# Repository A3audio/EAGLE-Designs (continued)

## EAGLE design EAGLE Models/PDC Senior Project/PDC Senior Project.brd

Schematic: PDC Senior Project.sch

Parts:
C1, C2: 18pF; C0805
C3, C4: 2.2uF; C0603
C5, C6, C7, C8, C9, C10, C11, C13, C14, C17, C21, C22: 220p; C0603
C12, C18, C19, C20: 100n; C0805
C16: 4.7nF; 0805
C23, C24: 10uF; C0603
D1: 1N4148; SOD-123
D2: 1N5819; SOD123
F1: 16V,0.25A; PTC-1206
F2, F3, F4, F5, F6, F7, F8, F9: PTC_FUSE2002920L; 2920L
H1, H2, H3, H4: MOUNT-PAD-ROUND#4-40-PAD; #4-40-PAD-ROUND
H7: ICSP; 2X3_SMD_FCI_54202-G30
IC1: AT90CAN128; TQFP64
IC2: MCP2551SO8; SO08
IC3: NUP2105L; SOT-23
IC5: FT232RL; SSOP28
L1: CS321613-100K; L3216C
LED2: RX; CHIPLED_0805
LED3: TX; CHIPLED_0805
M1, M2, M3, M4, M5, M6, M7, M8, M9, M11, M12: PSMN2R2-25YLC; SOT669(LFPAK_POWER-SO8)
Q1: 56P2859; HC49UP
R1, R3: 100K; R0805
R2, R7, R8, R9: 1k; R0805
R4, R11, R13, R15: 3k; R0603
R5, R10, R12, R14, R16, R18, R20, R22, R24, R26, R28, R30, R32, R34, R36, R38, R40, R49: 10k; R0603
R6: 1K; R0805
R17, R19, R21, R23, R25, R27, R29, R31, R33, R35, R37, R39, R48: 26k; R0603
R41, R42, R43, R44, R45, R46: 2k1; R0603
R47: 14k7; R0603
RS1, RS2, RS3, RS4: 0.002; WSL2726_RES
SJ1: SOLDERJUMPERNO; SJ_2S-NO
U1, U7, U8, U9, U10, U13, U14, U15, U16, U17, U18, U19: LT6100HMS8PBF; SOP65P490X110-8N
U2, U4, U5, U6: LT1716IS5PBF; SOT95P280X100-5N
U3, U11, U12: LT1161ISWPBF; SOIC127P1032X264-20N
U20: DG409DY-E3; SOIC127P600X175-16N
U21: AD5314WARMZ-REEL7; SOP50P490X110-10N
U22: LT1910IS8TRPBF; SOIC127P600X175-8N
U$2: MMPQ3904; SOIC16NB
U$3: MMPQ3906; SOIC16NB
U$4, U$6, U$8, U$10, U$12, U$14, U$16, U$18: 0.02; LVK2010
U$4V5V: MAX6350CSA; 8-SOIC
U$5, U$7, U$9, U$11, U$13, U$15, U$17, U$19: PSMN2R2-25YLC; SOT669(LFPAK_POWER-SO8)
U$20: DG407; PLCC28S
U$21: MCP970X; SOT23
U$22, U$23, U$24: AZ23C4V7-7-F; SOT23-3
U$25: SUPERSEAL1.0_60POS
U$26: NCP1117; SOT-223-4
VCC!: PWR; CHIPLED_0805

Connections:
5VREF: C4.1, IC1.62 (AREF), U$4V5V.P6
5V_REG_IN: C23.1, D2.C, U$26.3 (INPUT)
12V: C3.1, D2.A, F2.1, F3.1, F4.1, F5.1, F6.1, F7.1, F8.1, F9.1, R47.2, R48.1, RS1.PAS1 (1), RS2.PAS2 (2), RS3.PAS2 (2), RS4.PAS1 (1), U3.11 (V+_2), U3.13 (SEN_4), U3.15 (SEN_3), U3.17 (SEN_2), U3.19 (SEN_1), U3.20 (V+), U11.11 (V+_2), U11.13 (SEN_4), U11.15 (SEN_3), U11.17 (SEN_2), U11.19 (SEN_1), U11.20 (V+), U12.11 (V+_2), U12.13 (SEN_4), U12.15 (SEN_3), U12.17 (SEN_2), U12.19 (SEN_1), U12.20 (V+), U22.4 (IN), U22.6 (SENSE), U22.8 (V+), U$4V5V.P2, U$25.B1, U$25.B2, U$25.B8
ADC0: IC1.61 (PF0(ADC0)), U$20.28 (DA)
ADC1: IC1.60 (PF1(ADC1)), U$20.2 (DB)
ADC2: IC1.59 (PF2(ADC2)), U20.8 (DA)
ADC3: IC1.58 (PF3(ADC3)), U20.9 (DB)
ANALOG_EMERGENCY_SHUTDOWN: R10.2, U$3.9 (B4), U$3.11 (B3), U$3.13 (B2), U$3.15 (B1), U$25.A4
AVR_CS: IC1.10 ((SS)PB0), U21.10 (~SYNC)
AVR_MISO: IC1.13 ((MISO)PB3)
AVR_MOSI: IC1.12 ((MOSI)PB2), U21.8 (DIN)
AVR_SCK: H7.3, IC1.11 ((SCK)PB1), U21.9 (SCLK)
BAT_SENSE: IC1.54 (PF7(ADC7/TDI)), R48.2, R49.1
CAN_H: IC2.7 (CANH), IC3.2, U$25.A29
CAN_L: IC2.6 (CANL), IC3.1, U$25.A30
D+: IC5.15 (USBDP), U$25.A27
D-: IC5.16 (USBDM), U$25.A28
DTR: C20.1, IC5.2 (DTR#)
GND: C1.1, C2.1, C3.2, C4.2, C5.2, C6.2, C7.2, C8.2, C9.2, C10.2, C11.2, C12.2, C13.2, C14.2, C16.2, C17.2, C18.2, C19.2, C21.2, C22.2, C23.2, C24.2, H1.P$1, H2.P$1, H3.P$1, H4.P$1, H7.6, IC1.22 (GND), IC1.53 (GND_53), IC1.63 (GND(A)), IC2.2 (GND), IC3.3, IC5.7 (GND1), IC5.18 (GND2), IC5.21 (GND3), IC5.25 (AGND), IC5.26 (TEST), R3.2, R18.2, R20.2, R22.2, R24.2, R26.2, R28.2, R30.2, R32.2, R34.2, R36.2, R38.2, R40.2, R49.2, SJ1.1, U1.4 (VEE), U1.6 (A2), U1.7 (A4), U2.2 (V-), U3.1 (GND_2), U3.10 (GND), U4.2 (V-), U5.2 (V-), U6.2 (V-), U7.4 (VEE), U7.6 (A2), U7.7 (A4), U8.4 (VEE), U8.6 (A2), U8.7 (A4), U9.4 (VEE), U9.6 (A2), U9.7 (A4), U10.4 (VEE), U10.7 (A4), U11.1 (GND_2), U11.10 (GND), U12.1 (GND_2), U12.10 (GND), U13.4 (VEE), U13.7 (A4), U14.4 (VEE), U14.7 (A4), U15.4 (VEE), U15.7 (A4), U16.4 (VEE), U16.7 (A4), U17.4 (VEE), U17.7 (A4), U18.4 (VEE), U18.7 (A4), U19.4 (VEE), U19.7 (A4), U20.3 (V-), U20.15 (GND), U21.7 (GND), U22.1 (GND), U$2.10 (E4), U$2.12 (E3), U$2.14 (E2), U$2.16 (E1), U$4V5V.P4, U$20.12 (GND), U$20.27 (V-), U$21.3 (GND), U$22.3, U$23.3, U$24.3, U$25.A7, U$25.A8, U$25.A9, U$25.A15, U$25.A16, U$25.A17, U$25.A19, U$25.A24, U$25.A25, U$25.A32, U$25.A33, U$25.A34, U$25.B3, U$25.B9, U$25.B10, U$25.B14, U$25.B15, U$25.B16, U$25.B20, U$25.B21, U$25.B22, U$25.B23, U$26.1 (ADJUST), VCC!.C
HC1_ANALOG_BACKUP_REF: U2.4 (-IN), U21.2 (VOUTA)
HC1_DISCH_TRIGGER: R5.2, U2.1 (OUT), U$2.15 (B1)
HC1_GATE: M2.4 (G), M3.4 (G), U3.18 (GATE_1), U$2.1 (C1_A), U$2.2 (C1_B)
HC1_GATE_IN: U3.3 (INPUT_1), U$3.1 (C1_A), U$3.2 (C1_B)
HC1_ISENSE: R4.1, U1.5 (VOUT), U20.5 (S2A)
HC1_OUTPUT: M2.1 (S1), M2.2 (S2), M2.3 (S3), M3.1 (S1), M3.2 (S2), M3.3 (S3), R39.1, U$25.B5, U$25.B11
HC1_VSENSE: R39.2, R40.1, U20.12 (S2B)
HC2_ANALOG_BACKUP_REF: U4.4 (-IN), U21.3 (VOUTB)
HC2_DISCH_TRIGGER: R12.2, U4.1 (OUT), U$2.13 (B2)
HC2_GATE: M5.4 (G), M6.4 (G), U3.16 (GATE_2), U$2.3 (C2_A), U$2.4 (C2_B)
HC2_GATE_IN: U3.5 (INPUT_2), U$3.3 (C2_A), U$3.4 (C2_B)
HC2_ISENSE: R11.1, U7.5 (VOUT), U20.7 (S4A)
HC2_OUTPUT: M5.1 (S1), M5.2 (S2), M5.3 (S3), M6.1 (S1), M6.2 (S2), M6.3 (S3), R37.1, U$25.A2, U$25.A11
HC2_VSENSE: R37.2, R38.1, U20.10 (S4B)
HC3_ANALOG_BACKUP_REF: U5.4 (-IN), U21.4 (VOUTC)
HC3_DISCH_TRIGGER: R14.2, U5.1 (OUT), U$2.11 (B3)
HC3_GATE: M8.4 (G), M9.4 (G), U3.14 (GATE_3), U$2.5 (C3_A), U$2.6 (C3_B)
HC3_GATE_IN: U3.7 (INPUT_3), U$3.5 (C3_A), U$3.6 (C3_B)
HC3_ISENSE: R13.1, U8.5 (VOUT), U20.6 (S3A)
HC3_OUTPUT: M8.1 (S1), M8.2 (S2), M8.3 (S3), M9.1 (S1), M9.2 (S2), M9.3 (S3), R35.1, U$25.A3, U$25.A12
HC3_VSENSE: R35.2, R36.1, U20.11 (S3B)
HC4_ANALOG_BACKUP_REF: U6.4 (-IN), U21.6 (VOUTD)
HC4_DISCH_TRIGGER: R16.2, U6.1 (OUT), U$2.9 (B4)
HC4_GATE: M11.4 (G), M12.4 (G), U3.12 (GATE_4), U$2.7 (C4_A), U$2.8 (C4_B)
HC4_GATE_IN: U3.9 (INPUT_4), U$3.7 (C4_A), U$3.8 (C4_B)
HC4_ISENSE: R15.1, U9.5 (VOUT), U20.4 (S1A)
HC4_OUTPUT: M11.1 (S1), M11.2 (S2), M11.3 (S3), M12.1 (S1), M12.2 (S2), M12.3 (S3), R33.1, U$25.B6, U$25.B12
HC4_VSENSE: R33.2, R34.1, U20.13 (S1B)
INPUT1: R41.2, U$25.A14
INPUT2: R42.2, U$25.A23
INPUT3: R45.2, U$25.A31
INPUT4: R43.2, U$25.A22
INPUT5: R46.2, U$25.A20
INPUT6: R44.2, U$25.A21
INPUT_PIN_1: IC1.25 ((SCL/INT0)PD0), R41.1, U$22.2
INPUT_PIN_2: IC1.26 ((SDA/INT1)PD1), R42.1, U$22.1
INPUT_PIN_3: IC1.27 ((RXD1/INT2)PD2), R45.1, U$23.2
INPUT_PIN_4: IC1.28 ((TXD1/INT3)PD3), R43.1, U$23.1
INPUT_PIN_5: IC1.56 (PF5(ADC5/TMS)), R46.1, U$24.1
INPUT_PIN_6: IC1.55 (PF6(ADC6/TDO)), R44.1, U$24.2
INT_N: IC1.9 ((ICP3/INT7)PE7)
LC1_GATE: U11.18 (GATE_1), U$5.4 (G)
LC1_ISENSE: U10.5 (VOUT), U$20.19 (S1A)
LC1_OUTPUT: R17.1, U$5.1 (S1), U$5.2 (S2), U$5.3 (S3), U$25.A1
LC1_VSENSE: R17.2, R18.1, U$20.11 (S1B)
LC2_GATE: U11.16 (GATE_2), U$7.4 (G)
LC2_ISENSE: U13.5 (VOUT), U$20.20 (S2A)
LC2_OUTPUT: R19.1, U$7.1 (S1), U$7.2 (S2), U$7.3 (S3), U$25.A10
LC2_VSENSE: R19.2, R20.1, U$20.10 (S2B)
LC3_GATE: U11.14 (GATE_3), U$9.4 (G)
LC3_ISENSE: U14.5 (VOUT), U$20.21 (S3A)
LC3_OUTPUT: R21.1, U$9.1 (S1), U$9.2 (S2), U$9.3 (S3), U$25.A18
LC3_VSENSE: R21.2, R22.1, U$20.9 (S3B)
LC4_GATE: U11.12 (GATE_4), U$11.4 (G)
LC4_ISENSE: U15.5 (VOUT), U$20.22 (S4A)
LC4_OUTPUT: R23.1, U$11.1 (S1), U$11.2 (S2), U$11.3 (S3), U$25.A26
LC4_VSENSE: R23.2, R24.1, U$20.8 (S4B)
LC5_GATE: U12.18 (GATE_1), U$13.4 (G)
LC5_ISENSE: U16.5 (VOUT), U$20.23 (S5A)
LC5_OUTPUT: R25.1, U$13.1 (S1), U$13.2 (S2), U$13.3 (S3), U$25.B7
LC5_VSENSE: R25.2, R26.1, U$20.7 (S5B)
LC6_GATE: U12.16 (GATE_2), U$15.4 (G)
LC6_ISENSE: U17.5 (VOUT), U$20.24 (S6A)
LC6_OUTPUT: R27.1, U$15.1 (S1), U$15.2 (S2), U$15.3 (S3), U$25.B13
LC6_VSENSE: R27.2, R28.1, U$20.6 (S6B)
LC7_GATE: U12.14 (GATE_3), U$17.4 (G)
LC7_ISENSE: U18.5 (VOUT), U$20.25 (S7A)
LC7_OUTPUT: R29.1, U$17.1 (S1), U$17.2 (S2), U$17.3 (S3), U$25.B19
LC7_VSENSE: R29.2, R30.1, U$20.5 (S7B)
LC8_GATE: U12.12 (GATE_4), U$19.4 (G)
LC8_ISENSE: U19.5 (VOUT), U$20.26 (S8A)
LC8_OUTPUT: R31.1, U$19.1 (S1), U$19.2 (S2), U$19.3 (S3), U$25.B26
LC8_VSENSE: R31.2, R32.1, U$20.4 (S8B)
M8RXD: IC5.1 (TXD), R2.1
M8TXD: IC5.5 (RXD), R7.1
unnamed: M2.P$1 (D), M2.P$2 (D), M2.P$3 (D), M2.P$4 (D), M2.P$5 (D), M2.P$6 (D), M2.P$7 (D), M2.P$8 (D), M2.P$9 (D), M2.P$10 (D), M2.P$11 (D), M2.P$12 (D), M2.P$13 (D), M2.P$18 (D), M2.P$19 (D), M2.P$20 (D), M2.P$21 (D), M2.P$22 (D), M2.P$23 (D), M2.P$24 (D), M2.P$25 (D), M2.P$28 (D), M2.P$29 (D), M2.P$30 (D), M2.P$31 (D), M2.P$32 (D), M2.P$33 (D), M2.P$34 (D), M2.P$37 (D), M2.P$38 (D), M2.P$39 (D), M2.P$40 (D), M2.P$41 (D), M2.P$42 (D), M2.P$43 (D), M2.P$46 (D), M2.P$47 (D), M2.P$48 (D), M2.P$49 (D), M2.P$50 (D), M2.P$51 (D), M2.P$52 (D), M2.P$55 (D), M2.P$56 (D), M2.P$57 (D), M2.P$58 (D), M2.P$59 (D), M2.P$60 (D), M2.P$61 (D), M3.P$1 (D), M3.P$2 (D), M3.P$3 (D), M3.P$4 (D), M3.P$5 (D), M3.P$6 (D), M3.P$7 (D), M3.P$8 (D), M3.P$9 (D), M3.P$10 (D), M3.P$11 (D), M3.P$12 (D), M3.P$13 (D), M3.P$18 (D), M3.P$19 (D), M3.P$20 (D), M3.P$21 (D), M3.P$22 (D), M3.P$23 (D), M3.P$24 (D), M3.P$25 (D), M3.P$28 (D), M3.P$29 (D), M3.P$30 (D), M3.P$31 (D), M3.P$32 (D), M3.P$33 (D), M3.P$34 (D), M3.P$37 (D), M3.P$38 (D), M3.P$39 (D), M3.P$40 (D), M3.P$41 (D), M3.P$42 (D), M3.P$43 (D), M3.P$46 (D), M3.P$47 (D), M3.P$48 (D), M3.P$49 (D), M3.P$50 (D), M3.P$51 (D), M3.P$52 (D), M3.P$55 (D), M3.P$56 (D), M3.P$57 (D), M3.P$58 (D), M3.P$59 (D), M3.P$60 (D), M3.P$61 (D), RS1.PAS2 (2)
unnamed: RS1.SENSE1, U1.8 (VS+)
unnamed: RS1.SENSE2, U1.1 (VS-)
unnamed: C5.1, U1.3 (FIL)
unnamed: R4.2, R5.1, U2.3 (+IN)
unnamed: IC2.8 (RS), R3.1
unnamed: R11.2, R12.1, U4.3 (+IN)
unnamed: M5.P$1 (D), M5.P$2 (D), M5.P$3 (D), M5.P$4 (D), M5.P$5 (D), M5.P$6 (D), M5.P$7 (D), M5.P$8 (D), M5.P$9 (D), M5.P$10 (D), M5.P$11 (D), M5.P$12 (D), M5.P$13 (D), M5.P$18 (D), M5.P$19 (D), M5.P$20 (D), M5.P$21 (D), M5.P$22 (D), M5.P$23 (D), M5.P$24 (D), M5.P$25 (D), M5.P$28 (D), M5.P$29 (D), M5.P$30 (D), M5.P$31 (D), M5.P$32 (D), M5.P$33 (D), M5.P$34 (D), M5.P$37 (D), M5.P$38 (D), M5.P$39 (D), M5.P$40 (D), M5.P$41 (D), M5.P$42 (D), M5.P$43 (D), M5.P$46 (D), M5.P$47 (D), M5.P$48 (D), M5.P$49 (D), M5.P$50 (D), M5.P$51 (D), M5.P$52 (D), M5.P$55 (D), M5.P$56 (D), M5.P$57 (D), M5.P$58 (D), M5.P$59 (D), M5.P$60 (D), M5.P$61 (D), M6.P$1 (D), M6.P$2 (D), M6.P$3 (D), M6.P$4 (D), M6.P$5 (D), M6.P$6 (D), M6.P$7 (D), M6.P$8 (D), M6.P$9 (D), M6.P$10 (D), M6.P$11 (D), M6.P$12 (D), M6.P$13 (D), M6.P$18 (D), M6.P$19 (D), M6.P$20 (D), M6.P$21 (D), M6.P$22 (D), M6.P$23 (D), M6.P$24 (D), M6.P$25 (D), M6.P$28 (D), M6.P$29 (D), M6.P$30 (D), M6.P$31 (D), M6.P$32 (D), M6.P$33 (D), M6.P$34 (D), M6.P$37 (D), M6.P$38 (D), M6.P$39 (D), M6.P$40 (D), M6.P$41 (D), M6.P$42 (D), M6.P$43 (D), M6.P$46 (D), M6.P$47 (D), M6.P$48 (D), M6.P$49 (D), M6.P$50 (D), M6.P$51 (D), M6.P$52 (D), M6.P$55 (D), M6.P$56 (D), M6.P$57 (D), M6.P$58 (D), M6.P$59 (D), M6.P$60 (D), M6.P$61 (D), RS2.PAS1 (1)
unnamed: R6.1, VCC!.A
unnamed: RS2.SENSE2, U7.8 (VS+)
unnamed: C1.2, IC1.24 (XTAL1), Q1.1
unnamed: RS2.SENSE1, U7.1 (VS-)
unnamed: R13.2, R14.1, U5.3 (+IN)
unnamed: R15.2, R16.1, U6.3 (+IN)
unnamed: C6.1, U7.3 (FIL)
unnamed: M8.P$1 (D), M8.P$2 (D), M8.P$3 (D), M8.P$4 (D), M8.P$5 (D), M8.P$6 (D), M8.P$7 (D), M8.P$8 (D), M8.P$9 (D), M8.P$10 (D), M8.P$11 (D), M8.P$12 (D), M8.P$13 (D), M8.P$18 (D), M8.P$19 (D), M8.P$20 (D), M8.P$21 (D), M8.P$22 (D), M8.P$23 (D), M8.P$24 (D), M8.P$25 (D), M8.P$28 (D), M8.P$29 (D), M8.P$30 (D), M8.P$31 (D), M8.P$32 (D), M8.P$33 (D), M8.P$34 (D), M8.P$37 (D), M8.P$38 (D), M8.P$39 (D), M8.P$40 (D), M8.P$41 (D), M8.P$42 (D), M8.P$43 (D), M8.P$46 (D), M8.P$47 (D), M8.P$48 (D), M8.P$49 (D), M8.P$50 (D), M8.P$51 (D), M8.P$52 (D), M8.P$55 (D), M8.P$56 (D), M8.P$57 (D), M8.P$58 (D), M8.P$59 (D), M8.P$60 (D), M8.P$61 (D), M9.P$1 (D), M9.P$2 (D), M9.P$3 (D), M9.P$4 (D), M9.P$5 (D), M9.P$6 (D), M9.P$7 (D), M9.P$8 (D), M9.P$9 (D), M9.P$10 (D), M9.P$11 (D), M9.P$12 (D), M9.P$13 (D), M9.P$18 (D), M9.P$19 (D), M9.P$20 (D), M9.P$21 (D), M9.P$22 (D), M9.P$23 (D), M9.P$24 (D), M9.P$25 (D), M9.P$28 (D), M9.P$29 (D), M9.P$30 (D), M9.P$31 (D), M9.P$32 (D), M9.P$33 (D), M9.P$34 (D), M9.P$37 (D), M9.P$38 (D), M9.P$39 (D), M9.P$40 (D), M9.P$41 (D), M9.P$42 (D), M9.P$43 (D), M9.P$46 (D), M9.P$47 (D), M9.P$48 (D), M9.P$49 (D), M9.P$50 (D), M9.P$51 (D), M9.P$52 (D), M9.P$55 (D), M9.P$56 (D), M9.P$57 (D), M9.P$58 (D), M9.P$59 (D), M9.P$60 (D), M9.P$61 (D), RS3.PAS1 (1)
unnamed: RS3.SENSE2, U8.8 (VS+)
unnamed: RS3.SENSE1, U8.1 (VS-)
unnamed: C7.1, U8.3 (FIL)
unnamed: M11.P$1 (D), M11.P$2 (D), M11.P$3 (D), M11.P$4 (D), M11.P$5 (D), M11.P$6 (D), M11.P$7 (D), M11.P$8 (D), M11.P$9 (D), M11.P$10 (D), M11.P$11 (D), M11.P$12 (D), M11.P$13 (D), M11.P$18 (D), M11.P$19 (D), M11.P$20 (D), M11.P$21 (D), M11.P$22 (D), M11.P$23 (D), M11.P$24 (D), M11.P$25 (D), M11.P$28 (D), M11.P$29 (D), M11.P$30 (D), M11.P$31 (D), M11.P$32 (D), M11.P$33 (D), M11.P$34 (D), M11.P$37 (D), M11.P$38 (D), M11.P$39 (D), M11.P$40 (D), M11.P$41 (D), M11.P$42 (D), M11.P$43 (D), M11.P$46 (D), M11.P$47 (D), M11.P$48 (D), M11.P$49 (D), M11.P$50 (D), M11.P$51 (D), M11.P$52 (D), M11.P$55 (D), M11.P$56 (D), M11.P$57 (D), M11.P$58 (D), M11.P$59 (D), M11.P$60 (D), M11.P$61 (D), M12.P$1 (D), M12.P$2 (D), M12.P$3 (D), M12.P$4 (D), M12.P$5 (D), M12.P$6 (D), M12.P$7 (D), M12.P$8 (D), M12.P$9 (D), M12.P$10 (D), M12.P$11 (D), M12.P$12 (D), M12.P$13 (D), M12.P$18 (D), M12.P$19 (D), M12.P$20 (D), M12.P$21 (D), M12.P$22 (D), M12.P$23 (D), M12.P$24 (D), M12.P$25 (D), M12.P$28 (D), M12.P$29 (D), M12.P$30 (D), M12.P$31 (D), M12.P$32 (D), M12.P$33 (D), M12.P$34 (D), M12.P$37 (D), M12.P$38 (D), M12.P$39 (D), M12.P$40 (D), M12.P$41 (D), M12.P$42 (D), M12.P$43 (D), M12.P$46 (D), M12.P$47 (D), M12.P$48 (D), M12.P$49 (D), M12.P$50 (D), M12.P$51 (D), M12.P$52 (D), M12.P$55 (D), M12.P$56 (D), M12.P$57 (D), M12.P$58 (D), M12.P$59 (D), M12.P$60 (D), M12.P$61 (D), RS4.PAS2 (2)
unnamed: IC1.64 (AVCC), L1.2
unnamed: RS4.SENSE1, U9.8 (VS+)
unnamed: RS4.SENSE2, U9.1 (VS-)
unnamed: C8.1, U9.3 (FIL)
unnamed: F2.2, U$4.V1
unnamed: U$4.V2, U$5.P$1 (D), U$5.P$2 (D), U$5.P$3 (D), U$5.P$4 (D), U$5.P$5 (D), U$5.P$6 (D), U$5.P$7 (D), U$5.P$8 (D), U$5.P$9 (D), U$5.P$10 (D), U$5.P$11 (D), U$5.P$12 (D), U$5.P$13 (D), U$5.P$18 (D), U$5.P$19 (D), U$5.P$20 (D), U$5.P$21 (D), U$5.P$22 (D), U$5.P$23 (D), U$5.P$24 (D), U$5.P$25 (D), U$5.P$28 (D), U$5.P$29 (D), U$5.P$30 (D), U$5.P$31 (D), U$5.P$32 (D), U$5.P$33 (D), U$5.P$34 (D), U$5.P$37 (D), U$5.P$38 (D), U$5.P$39 (D), U$5.P$40 (D), U$5.P$41 (D), U$5.P$42 (D), U$5.P$43 (D), U$5.P$46 (D), U$5.P$47 (D), U$5.P$48 (D), U$5.P$49 (D), U$5.P$50 (D), U$5.P$51 (D), U$5.P$52 (D), U$5.P$55 (D), U$5.P$56 (D), U$5.P$57 (D), U$5.P$58 (D), U$5.P$59 (D), U$5.P$60 (D), U$5.P$61 (D)
unnamed: U10.1 (VS-), U$4.I2
unnamed: U10.8 (VS+), U$4.I1
unnamed: F3.2, U$6.V1
unnamed: C9.1, U10.3 (FIL)
unnamed: IC5.23 (GPIO1), LED2.C
unnamed: U$6.V2, U$7.P$1 (D), U$7.P$2 (D), U$7.P$3 (D), U$7.P$4 (D), U$7.P$5 (D), U$7.P$6 (D), U$7.P$7 (D), U$7.P$8 (D), U$7.P$9 (D), U$7.P$10 (D), U$7.P$11 (D), U$7.P$12 (D), U$7.P$13 (D), U$7.P$18 (D), U$7.P$19 (D), U$7.P$20 (D), U$7.P$21 (D), U$7.P$22 (D), U$7.P$23 (D), U$7.P$24 (D), U$7.P$25 (D), U$7.P$28 (D), U$7.P$29 (D), U$7.P$30 (D), U$7.P$31 (D), U$7.P$32 (D), U$7.P$33 (D), U$7.P$34 (D), U$7.P$37 (D), U$7.P$38 (D), U$7.P$39 (D), U$7.P$40 (D), U$7.P$41 (D), U$7.P$42 (D), U$7.P$43 (D), U$7.P$46 (D), U$7.P$47 (D), U$7.P$48 (D), U$7.P$49 (D), U$7.P$50 (D), U$7.P$51 (D), U$7.P$52 (D), U$7.P$55 (D), U$7.P$56 (D), U$7.P$57 (D), U$7.P$58 (D), U$7.P$59 (D), U$7.P$60 (D), U$7.P$61 (D)
unnamed: IC5.22 (GPIO0), LED3.C
unnamed: LED2.A, R8.1
unnamed: LED3.A, R9.1
unnamed: U13.8 (VS+), U$6.I1
unnamed: C10.1, U13.3 (FIL)
unnamed: U13.1 (VS-), U$6.I2
unnamed: F4.2, U$8.V1
unnamed: U$8.V2, U$9.P$1 (D), U$9.P$2 (D), U$9.P$3 (D), U$9.P$4 (D), U$9.P$5 (D), U$9.P$6 (D), U$9.P$7 (D), U$9.P$8 (D), U$9.P$9 (D), U$9.P$10 (D), U$9.P$11 (D), U$9.P$12 (D), U$9.P$13 (D), U$9.P$18 (D), U$9.P$19 (D), U$9.P$20 (D), U$9.P$21 (D), U$9.P$22 (D), U$9.P$23 (D), U$9.P$24 (D), U$9.P$25 (D), U$9.P$28 (D), U$9.P$29 (D), U$9.P$30 (D), U$9.P$31 (D), U$9.P$32 (D), U$9.P$33 (D), U$9.P$34 (D), U$9.P$37 (D), U$9.P$38 (D), U$9.P$39 (D), U$9.P$40 (D), U$9.P$41 (D), U$9.P$42 (D), U$9.P$43 (D), U$9.P$46 (D), U$9.P$47 (D), U$9.P$48 (D), U$9.P$49 (D), U$9.P$50 (D), U$9.P$51 (D), U$9.P$52 (D), U$9.P$55 (D), U$9.P$56 (D), U$9.P$57 (D), U$9.P$58 (D), U$9.P$59 (D), U$9.P$60 (D), U$9.P$61 (D)
unnamed: U14.8 (VS+), U$8.I1
unnamed: C11.1, U14.3 (FIL)
unnamed: U14.1 (VS-), U$8.I2
unnamed: F5.2, U$10.V1
unnamed: U$10.V2, U$11.P$1 (D), U$11.P$2 (D), U$11.P$3 (D), U$11.P$4 (D), U$11.P$5 (D), U$11.P$6 (D), U$11.P$7 (D), U$11.P$8 (D), U$11.P$9 (D), U$11.P$10 (D), U$11.P$11 (D), U$11.P$12 (D), U$11.P$13 (D), U$11.P$18 (D), U$11.P$19 (D), U$11.P$20 (D), U$11.P$21 (D), U$11.P$22 (D), U$11.P$23 (D), U$11.P$24 (D), U$11.P$25 (D), U$11.P$28 (D), U$11.P$29 (D), U$11.P$30 (D), U$11.P$31 (D), U$11.P$32 (D), U$11.P$33 (D), U$11.P$34 (D), U$11.P$37 (D), U$11.P$38 (D), U$11.P$39 (D), U$11.P$40 (D), U$11.P$41 (D), U$11.P$42 (D), U$11.P$43 (D), U$11.P$46 (D), U$11.P$47 (D), U$11.P$48 (D), U$11.P$49 (D), U$11.P$50 (D), U$11.P$51 (D), U$11.P$52 (D), U$11.P$55 (D), U$11.P$56 (D), U$11.P$57 (D), U$11.P$58 (D), U$11.P$59 (D), U$11.P$60 (D), U$11.P$61 (D)
unnamed: U15.8 (VS+), U$10.I1
unnamed: C13.1, U15.3 (FIL)
unnamed: U15.1 (VS-), U$10.I2
unnamed: F6.2, U$12.V1
unnamed: U$12.V2, U$13.P$1 (D), U$13.P$2 (D), U$13.P$3 (D), U$13.P$4 (D), U$13.P$5 (D), U$13.P$6 (D), U$13.P$7 (D), U$13.P$8 (D), U$13.P$9 (D), U$13.P$10 (D), U$13.P$11 (D), U$13.P$12 (D), U$13.P$13 (D), U$13.P$18 (D), U$13.P$19 (D), U$13.P$20 (D), U$13.P$21 (D), U$13.P$22 (D), U$13.P$23 (D), U$13.P$24 (D), U$13.P$25 (D), U$13.P$28 (D), U$13.P$29 (D), U$13.P$30 (D), U$13.P$31 (D), U$13.P$32 (D), U$13.P$33 (D), U$13.P$34 (D), U$13.P$37 (D), U$13.P$38 (D), U$13.P$39 (D), U$13.P$40 (D), U$13.P$41 (D), U$13.P$42 (D), U$13.P$43 (D), U$13.P$46 (D), U$13.P$47 (D), U$13.P$48 (D), U$13.P$49 (D), U$13.P$50 (D), U$13.P$51 (D), U$13.P$52 (D), U$13.P$55 (D), U$13.P$56 (D), U$13.P$57 (D), U$13.P$58 (D), U$13.P$59 (D), U$13.P$60 (D), U$13.P$61 (D)
unnamed: U16.8 (VS+), U$12.I1
unnamed: C14.1, U16.3 (FIL)
unnamed: U16.1 (VS-), U$12.I2
unnamed: F7.2, U$14.V1
unnamed: U$14.V2, U$15.P$1 (D), U$15.P$2 (D), U$15.P$3 (D), U$15.P$4 (D), U$15.P$5 (D), U$15.P$6 (D), U$15.P$7 (D), U$15.P$8 (D), U$15.P$9 (D), U$15.P$10 (D), U$15.P$11 (D), U$15.P$12 (D), U$15.P$13 (D), U$15.P$18 (D), U$15.P$19 (D), U$15.P$20 (D), U$15.P$21 (D), U$15.P$22 (D), U$15.P$23 (D), U$15.P$24 (D), U$15.P$25 (D), U$15.P$28 (D), U$15.P$29 (D), U$15.P$30 (D), U$15.P$31 (D), U$15.P$32 (D), U$15.P$33 (D), U$15.P$34 (D), U$15.P$37 (D), U$15.P$38 (D), U$15.P$39 (D), U$15.P$40 (D), U$15.P$41 (D), U$15.P$42 (D), U$15.P$43 (D), U$15.P$46 (D), U$15.P$47 (D), U$15.P$48 (D), U$15.P$49 (D), U$15.P$50 (D), U$15.P$51 (D), U$15.P$52 (D), U$15.P$55 (D), U$15.P$56 (D), U$15.P$57 (D), U$15.P$58 (D), U$15.P$59 (D), U$15.P$60 (D), U$15.P$61 (D)
unnamed: U17.8 (VS+), U$14.I1
unnamed: C17.1, U17.3 (FIL)
unnamed: U17.1 (VS-), U$14.I2
unnamed: F8.2, U$16.V1
unnamed: U$16.V2, U$17.P$1 (D), U$17.P$2 (D), U$17.P$3 (D), U$17.P$4 (D), U$17.P$5 (D), U$17.P$6 (D), U$17.P$7 (D), U$17.P$8 (D), U$17.P$9 (D), U$17.P$10 (D), U$17.P$11 (D), U$17.P$12 (D), U$17.P$13 (D), U$17.P$18 (D), U$17.P$19 (D), U$17.P$20 (D), U$17.P$21 (D), U$17.P$22 (D), U$17.P$23 (D), U$17.P$24 (D), U$17.P$25 (D), U$17.P$28 (D), U$17.P$29 (D), U$17.P$30 (D), U$17.P$31 (D), U$17.P$32 (D), U$17.P$33 (D), U$17.P$34 (D), U$17.P$37 (D), U$17.P$38 (D), U$17.P$39 (D), U$17.P$40 (D), U$17.P$41 (D), U$17.P$42 (D), U$17.P$43 (D), U$17.P$46 (D), U$17.P$47 (D), U$17.P$48 (D), U$17.P$49 (D), U$17.P$50 (D), U$17.P$51 (D), U$17.P$52 (D), U$17.P$55 (D), U$17.P$56 (D), U$17.P$57 (D), U$17.P$58 (D), U$17.P$59 (D), U$17.P$60 (D), U$17.P$61 (D)
unnamed: U18.8 (VS+), U$16.I1
unnamed: C21.1, U18.3 (FIL)
unnamed: U18.1 (VS-), U$16.I2
unnamed: F9.2, U$18.V1
unnamed: U$18.V2, U$19.P$1 (D), U$19.P$2 (D), U$19.P$3 (D), U$19.P$4 (D), U$19.P$5 (D), U$19.P$6 (D), U$19.P$7 (D), U$19.P$8 (D), U$19.P$9 (D), U$19.P$10 (D), U$19.P$11 (D), U$19.P$12 (D), U$19.P$13 (D), U$19.P$18 (D), U$19.P$19 (D), U$19.P$20 (D), U$19.P$21 (D), U$19.P$22 (D), U$19.P$23 (D), U$19.P$24 (D), U$19.P$25 (D), U$19.P$28 (D), U$19.P$29 (D), U$19.P$30 (D), U$19.P$31 (D), U$19.P$32 (D), U$19.P$33 (D), U$19.P$34 (D), U$19.P$37 (D), U$19.P$38 (D), U$19.P$39 (D), U$19.P$40 (D), U$19.P$41 (D), U$19.P$42 (D), U$19.P$43 (D), U$19.P$46 (D), U$19.P$47 (D), U$19.P$48 (D), U$19.P$49 (D), U$19.P$50 (D), U$19.P$51 (D), U$19.P$52 (D), U$19.P$55 (D), U$19.P$56 (D), U$19.P$57 (D), U$19.P$58 (D), U$19.P$59 (D), U$19.P$60 (D), U$19.P$61 (D)
unnamed: U19.8 (VS+), U$18.I1
unnamed: C22.1, U19.3 (FIL)
unnamed: U19.1 (VS-), U$18.I2
unnamed: R47.1, U22.3 (~FAULT)
PA0: IC1.51 ((AD0)PA0), U11.9 (INPUT_4)
PA1: IC1.50 ((AD1)PA1), U12.3 (INPUT_1)
PA2: IC1.49 ((AD2)PA2), U12.5 (INPUT_2)
PA3: IC1.48 ((AD3)PA3), U12.7 (INPUT_3)
PA4: IC1.47 ((AD4)PA4), U12.9 (INPUT_4)
PA5: IC1.46 ((AD5)PA5)
PA6: IC1.45 ((AD6)PA6)
PA7: IC1.44 ((AD7)PA7)
PB4(PWM): IC1.14 ((OC2A)PB4), U$3.16 (E1)
PB5(PWM): IC1.15 ((OC1A)PB5), U$3.14 (E2)
PB6(PWM): IC1.16 ((OC1B)PB6), U$3.12 (E3)
PB7(PWM): IC1.17 ((OC0A/OC1C)PB7), U$3.10 (E4)
PC0: IC1.35 ((A8)PC0), U20.1 (A0), U$20.17 (A0)
PC1: IC1.36 ((A9)PC1), U20.16 (A1), U$20.16 (A1)
PC2: IC1.37 ((A10)PC2), U$20.15 (A2)
PC3: IC1.38 ((A11)PC3)
PC4: IC1.39 ((A12)PC4)
PC5: IC1.40 ((A13)PC5)
PC6: IC1.41 ((A14)PC6)
PC7: IC1.42 ((A15/CLKO)PC7)
PD4: IC1.29 ((ICP1)PD4)
PD7: IC1.32 ((T0)PD7)
PE2: IC1.4 ((XCK0/AIN0)PE2)
PE3(PWM): IC1.5 ((OC3A/AIN1)PE3), U11.3 (INPUT_1)
PE4(PWM): IC1.6 ((OC3B/INT4)PE4), U11.5 (INPUT_2)
PE5(PWM): IC1.7 ((OC3C/INT5)PE5), U11.7 (INPUT_3)
PE6: IC1.8 ((T3/INT6)PE6)
PG0: IC1.33 (PG0(WR))
PG1: IC1.34 (PG1(RD))
PG2: IC1.43 (PG2(ALE))
RECTIFIER_GATE: M1.4 (G), M4.4 (G), M7.4 (G), U22.5 (GATE)
RECTIFIER_IN: M1.P$1 (D), M1.P$2 (D), M1.P$3 (D), M1.P$4 (D), M1.P$5 (D), M1.P$6 (D), M1.P$7 (D), M1.P$8 (D), M1.P$9 (D), M1.P$10 (D), M1.P$11 (D), M1.P$12 (D), M1.P$13 (D), M1.P$18 (D), M1.P$19 (D), M1.P$20 (D), M1.P$21 (D), M1.P$22 (D), M1.P$23 (D), M1.P$24 (D), M1.P$25 (D), M1.P$28 (D), M1.P$29 (D), M1.P$30 (D), M1.P$31 (D), M1.P$32 (D), M1.P$33 (D), M1.P$34 (D), M1.P$37 (D), M1.P$38 (D), M1.P$39 (D), M1.P$40 (D), M1.P$41 (D), M1.P$42 (D), M1.P$43 (D), M1.P$46 (D), M1.P$47 (D), M1.P$48 (D), M1.P$49 (D), M1.P$50 (D), M1.P$51 (D), M1.P$52 (D), M1.P$55 (D), M1.P$56 (D), M1.P$57 (D), M1.P$58 (D), M1.P$59 (D), M1.P$60 (D), M1.P$61 (D), M4.P$1 (D), M4.P$2 (D), M4.P$3 (D), M4.P$4 (D), M4.P$5 (D), M4.P$6 (D), M4.P$7 (D), M4.P$8 (D), M4.P$9 (D), M4.P$10 (D), M4.P$11 (D), M4.P$12 (D), M4.P$13 (D), M4.P$18 (D), M4.P$19 (D), M4.P$20 (D), M4.P$21 (D), M4.P$22 (D), M4.P$23 (D), M4.P$24 (D), M4.P$25 (D), M4.P$28 (D), M4.P$29 (D), M4.P$30 (D), M4.P$31 (D), M4.P$32 (D), M4.P$33 (D), M4.P$34 (D), M4.P$37 (D), M4.P$38 (D), M4.P$39 (D), M4.P$40 (D), M4.P$41 (D), M4.P$42 (D), M4.P$43 (D), M4.P$46 (D), M4.P$47 (D), M4.P$48 (D), M4.P$49 (D), M4.P$50 (D), M4.P$51 (D), M4.P$52 (D), M4.P$55 (D), M4.P$56 (D), M4.P$57 (D), M4.P$58 (D), M4.P$59 (D), M4.P$60 (D), M4.P$61 (D), M7.P$1 (D), M7.P$2 (D), M7.P$3 (D), M7.P$4 (D), M7.P$5 (D), M7.P$6 (D), M7.P$7 (D), M7.P$8 (D), M7.P$9 (D), M7.P$10 (D), M7.P$11 (D), M7.P$12 (D), M7.P$13 (D), M7.P$18 (D), M7.P$19 (D), M7.P$20 (D), M7.P$21 (D), M7.P$22 (D), M7.P$23 (D), M7.P$24 (D), M7.P$25 (D), M7.P$28 (D), M7.P$29 (D), M7.P$30 (D), M7.P$31 (D), M7.P$32 (D), M7.P$33 (D), M7.P$34 (D), M7.P$37 (D), M7.P$38 (D), M7.P$39 (D), M7.P$40 (D), M7.P$41 (D), M7.P$42 (D), M7.P$43 (D), M7.P$46 (D), M7.P$47 (D), M7.P$48 (D), M7.P$49 (D), M7.P$50 (D), M7.P$51 (D), M7.P$52 (D), M7.P$55 (D), M7.P$56 (D), M7.P$57 (D), M7.P$58 (D), M7.P$59 (D), M7.P$60 (D), M7.P$61 (D), U$25.B17, U$25.B24
RECTIFIER_OUT: M1.1 (S1), M1.2 (S2), M1.3 (S3), M4.1 (S1), M4.2 (S2), M4.3 (S3), M7.1 (S1), M7.2 (S2), M7.3 (S3), U$25.B18, U$25.B25
RESET: C16.1, C20.2, D1.A, H7.5, IC1.20 (RESET), R1.1, SJ1.2
RX: H7.4, IC1.2 ((RXD0/PDI)PE0), R2.2
RXCAN: IC1.31 ((RXCAN/T1)PD6), IC2.4 (RXD)
TEMP_SENSE: IC1.57 (PF4(ADC4/TCK)), U$21.2 (VOUT)
TX: H7.1, IC1.3 ((TXD0/PDO)PE1), R7.2
TXCAN: IC1.30 ((TXCAN/XCK1)PD5), IC2.1 (TXD)
USB_V_IN: F1.2, U$25.A13
VCC: C12.1, C19.1, C24.1, D1.C, F1.1, H7.2, IC1.21 (VCC), IC1.52 (VCC_52), IC2.3 (VCC), IC5.4 (VCCIO), IC5.19 (RESET#), IC5.20 (VCC5I), L1.1, R1.2, R6.2, R8.2, R9.2, R10.1, U1.2 (VCC), U2.5 (V+), U4.5 (V+), U5.5 (V+), U6.5 (V+), U7.2 (VCC), U8.2 (VCC), U9.2 (VCC), U10.2 (VCC), U13.2 (VCC), U14.2 (VCC), U15.2 (VCC), U16.2 (VCC), U17.2 (VCC), U18.2 (VCC), U19.2 (VCC), U20.2 (EN), U20.14 (V+), U21.1 (VDD), U21.5 (REFIN), U$20.1 (V+), U$20.18 (EN), U$21.1 (VDD), U$26.2 (OUTPUT), U$26.4 (OUTPUT)
VCC3O: C18.1, IC5.17 (VCC30)
XTAL1: C2.2, IC1.23 (XTAL2), Q1.2

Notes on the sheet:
POWER SUPPLY
CAN
RESET PIN
AVR CONNECTIONS
FTDI Interface
Modified from Arduino Duemilanove schematics
Copyright (C) 2009 M. Banzi, D. Cuartielles, T. Igoe, G. Martino, D. Mellis
Arduino material originally licensed CC-BY-SA 3.0
Connectors
E-Stop and gate drive
Analog HC Overcurrent Redundancy
High Current Outputs
Low Current Outputs and Gate Drive
Signal to ADC Multiplexing
Temperature Sensing
Input Current Limiting
Mounting Holes
Rectifier Shutdown
MAX6350CSA

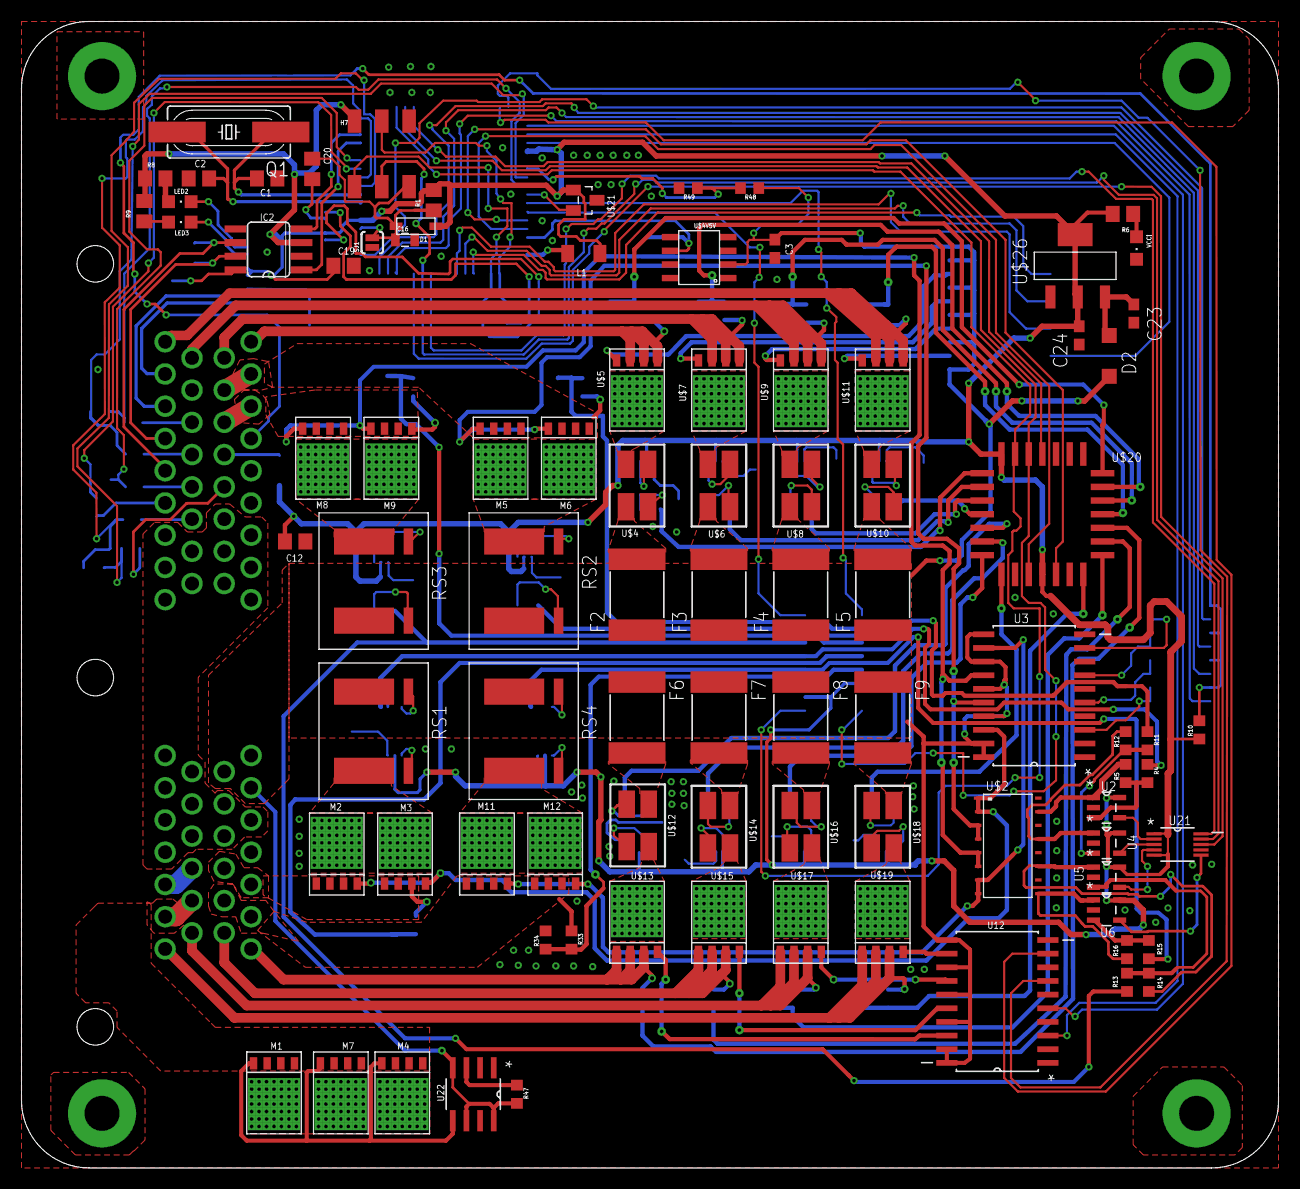
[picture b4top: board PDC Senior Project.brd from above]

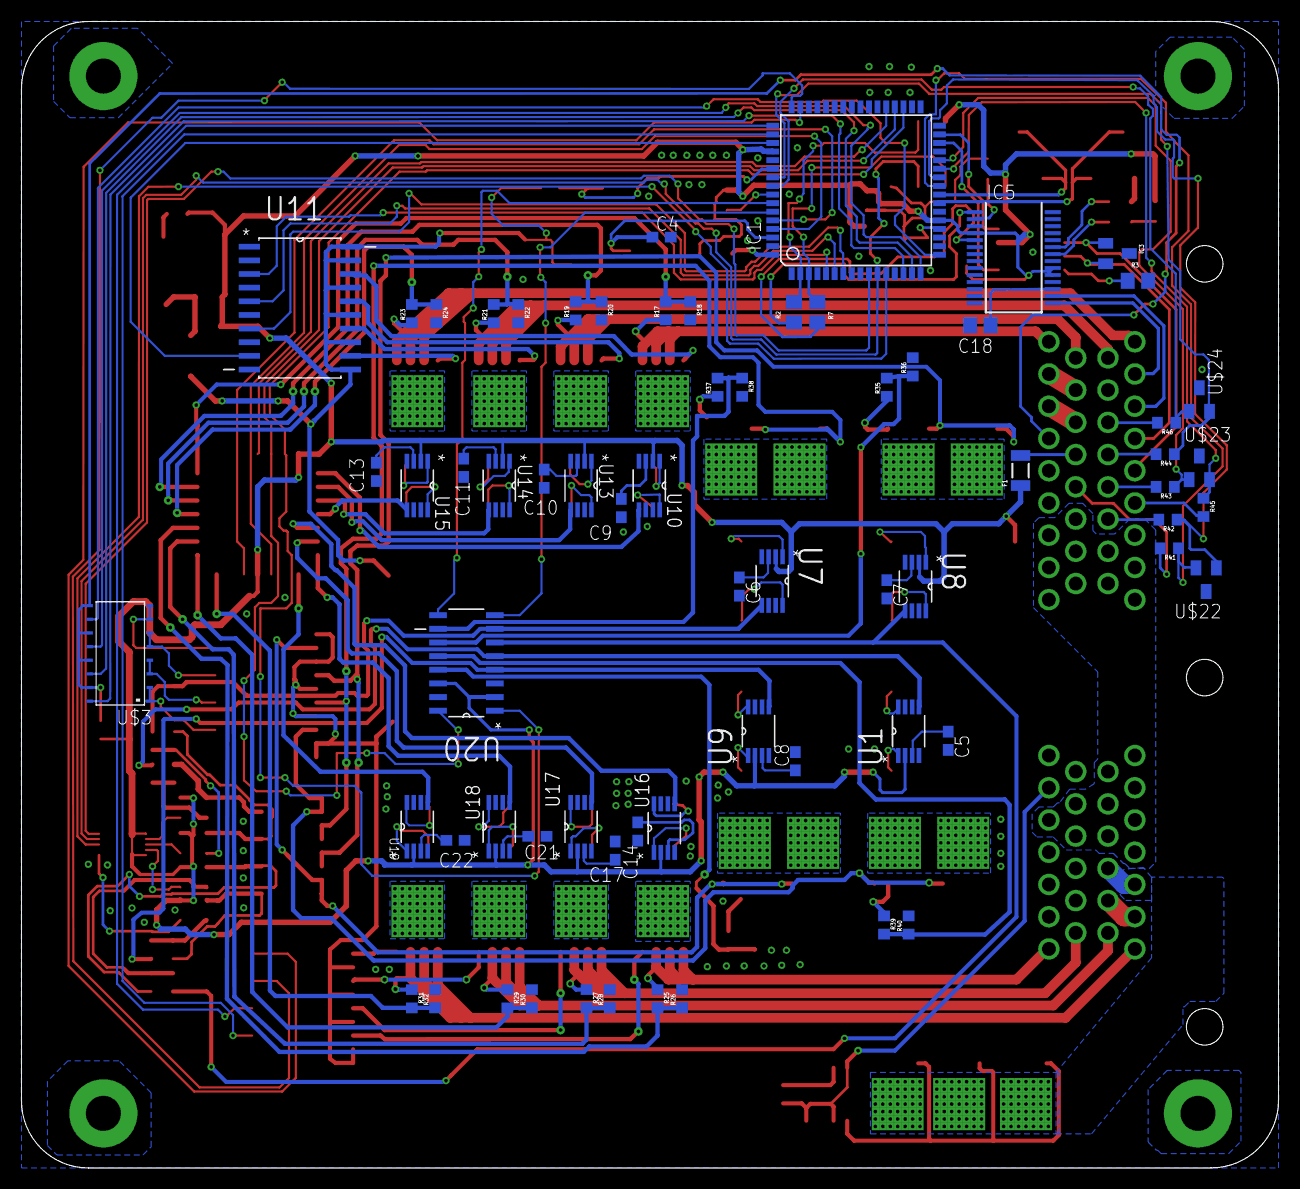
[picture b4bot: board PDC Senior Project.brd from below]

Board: 2 copper layers, 117.0 x 106.7 mm, 161 parts (67 on the bottom side), 189 nets.

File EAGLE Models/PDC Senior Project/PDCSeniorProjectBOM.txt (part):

Partlist exported from C:/Users/Daniel Baron/Documents/GitHub/FormulaEagleDesigns/EAGLE-Designs/EAGLE Models/PDC Senior Project/PDC Senior Project.sch at 3/17/2017 3:38 PM

Qty Value                    Device                   Package                 Parts                                                                                     Description                                                                         MF         MPN               OC_FARNELL OC_NEWARK PACKAGE   SUPPLIER         
2                            C-USC0603                C0603                   C23, C24                                                                                  CAPACITOR, American symbol                                                                                                                                       
4   0.002                    WSL2726_RES              WSL2726_RES             RS1, RS2, RS3, RS4                                                                                                                                                                                                                                         
8   0.02                     LVK_SERIES               LVK2010                 U$4, U$6, U$8, U$10, U$12, U$14, U$16, U$18                                                                                                                                                                                                                
2   100K                     R-US_R0805               R0805                   R1, R3                                                                                    RESISTOR, American symbol                                                                                                                                        
4   100n                     C-USC0805                C0805                   C12, C18, C19, C20                                                                        CAPACITOR, American symbol                                                                                                                                       
18  10k                      R-US_R0603               R0603                   R5, R10, R12, R14, R16, R18, R20, R22, R24, R26, R28, R30, R32, R34, R36, R38, R40, R49   RESISTOR, American symbol                                                                                                                                        
1   14k7                     R-US_R0603               R0603                   R47                                                                                       RESISTOR, American symbol                                                                                                                                        
1   16V,0.25A                PTCSMD                   PTC-1206                F1                                                                                        Resettable Fuse PTC                                                                                                                                              
2   18pF                     C-USC0805                C0805                   C1, C2                                                                                    CAPACITOR, American symbol                                                                                                                                       
1   1K                       R-US_R0805               R0805                   R6                                                                                        RESISTOR, American symbol                                                                                                                                        
1   1N4148                   DIODESOD-123             SOD-123                 D1                                                                                        Diode                                                                                                                                                            
1   1N5819                   1N5819-BSOD123           SOD123                  D2                                                                                        1.0A SCHOTTKY BARRIER RECTIFIER                                                                                                                                  
4   1k                       R-US_R0805               R0805                   R2, R7, R8, R9                                                                            RESISTOR, American symbol                                                                                                                                        
2   2.2uF                    C-USC0603                C0603                   C3, C4                                                                                    CAPACITOR, American symbol                                                                                                                                       
12  220p                     C-USC0603                C0603                   C5, C6, C7, C8, C9, C10, C11, C13, C14, C17, C21, C22                                     CAPACITOR, American symbol                                                                                                                                       
13  26k                      R-US_R0603               R0603                   R17, R19, R21, R23, R25, R27, R29, R31, R33, R35, R37, R39, R48                           RESISTOR, American symbol                                                                                                                                        
6   2k1                      R-US_R0603               R0603                   R41, R42, R43, R44, R45, R46                                                              RESISTOR, American symbol                                                                                                                                        
4   3k                       R-US_R0603               R0603                   R4, R11, R13, R15                                                                         RESISTOR, American symbol                                                                                                                                        
1   4.7nF                    CAP0805                  0805                    C16                                                                                       Capacitor                                                                                                                                                        
1   56P2859                  CRYSTALSMD               HC49UP                  Q1                                                                                        Various standard crystals. Proven footprints. Spark Fun Electronics SKU : COM-00534                                                                              
1   AD5314WARMZ-REEL7        AD5314WARMZ-REEL7        SOP50P490X110-10N       U21                                                                                       DAC                                                                                            AD5314WARMZ-REEL7 -          11R1003   MSOP-10   Analog Devices   
1   AT90CAN128               AT90CAN128               TQFP64                  IC1                                                                                                                                                                                                                                                        
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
